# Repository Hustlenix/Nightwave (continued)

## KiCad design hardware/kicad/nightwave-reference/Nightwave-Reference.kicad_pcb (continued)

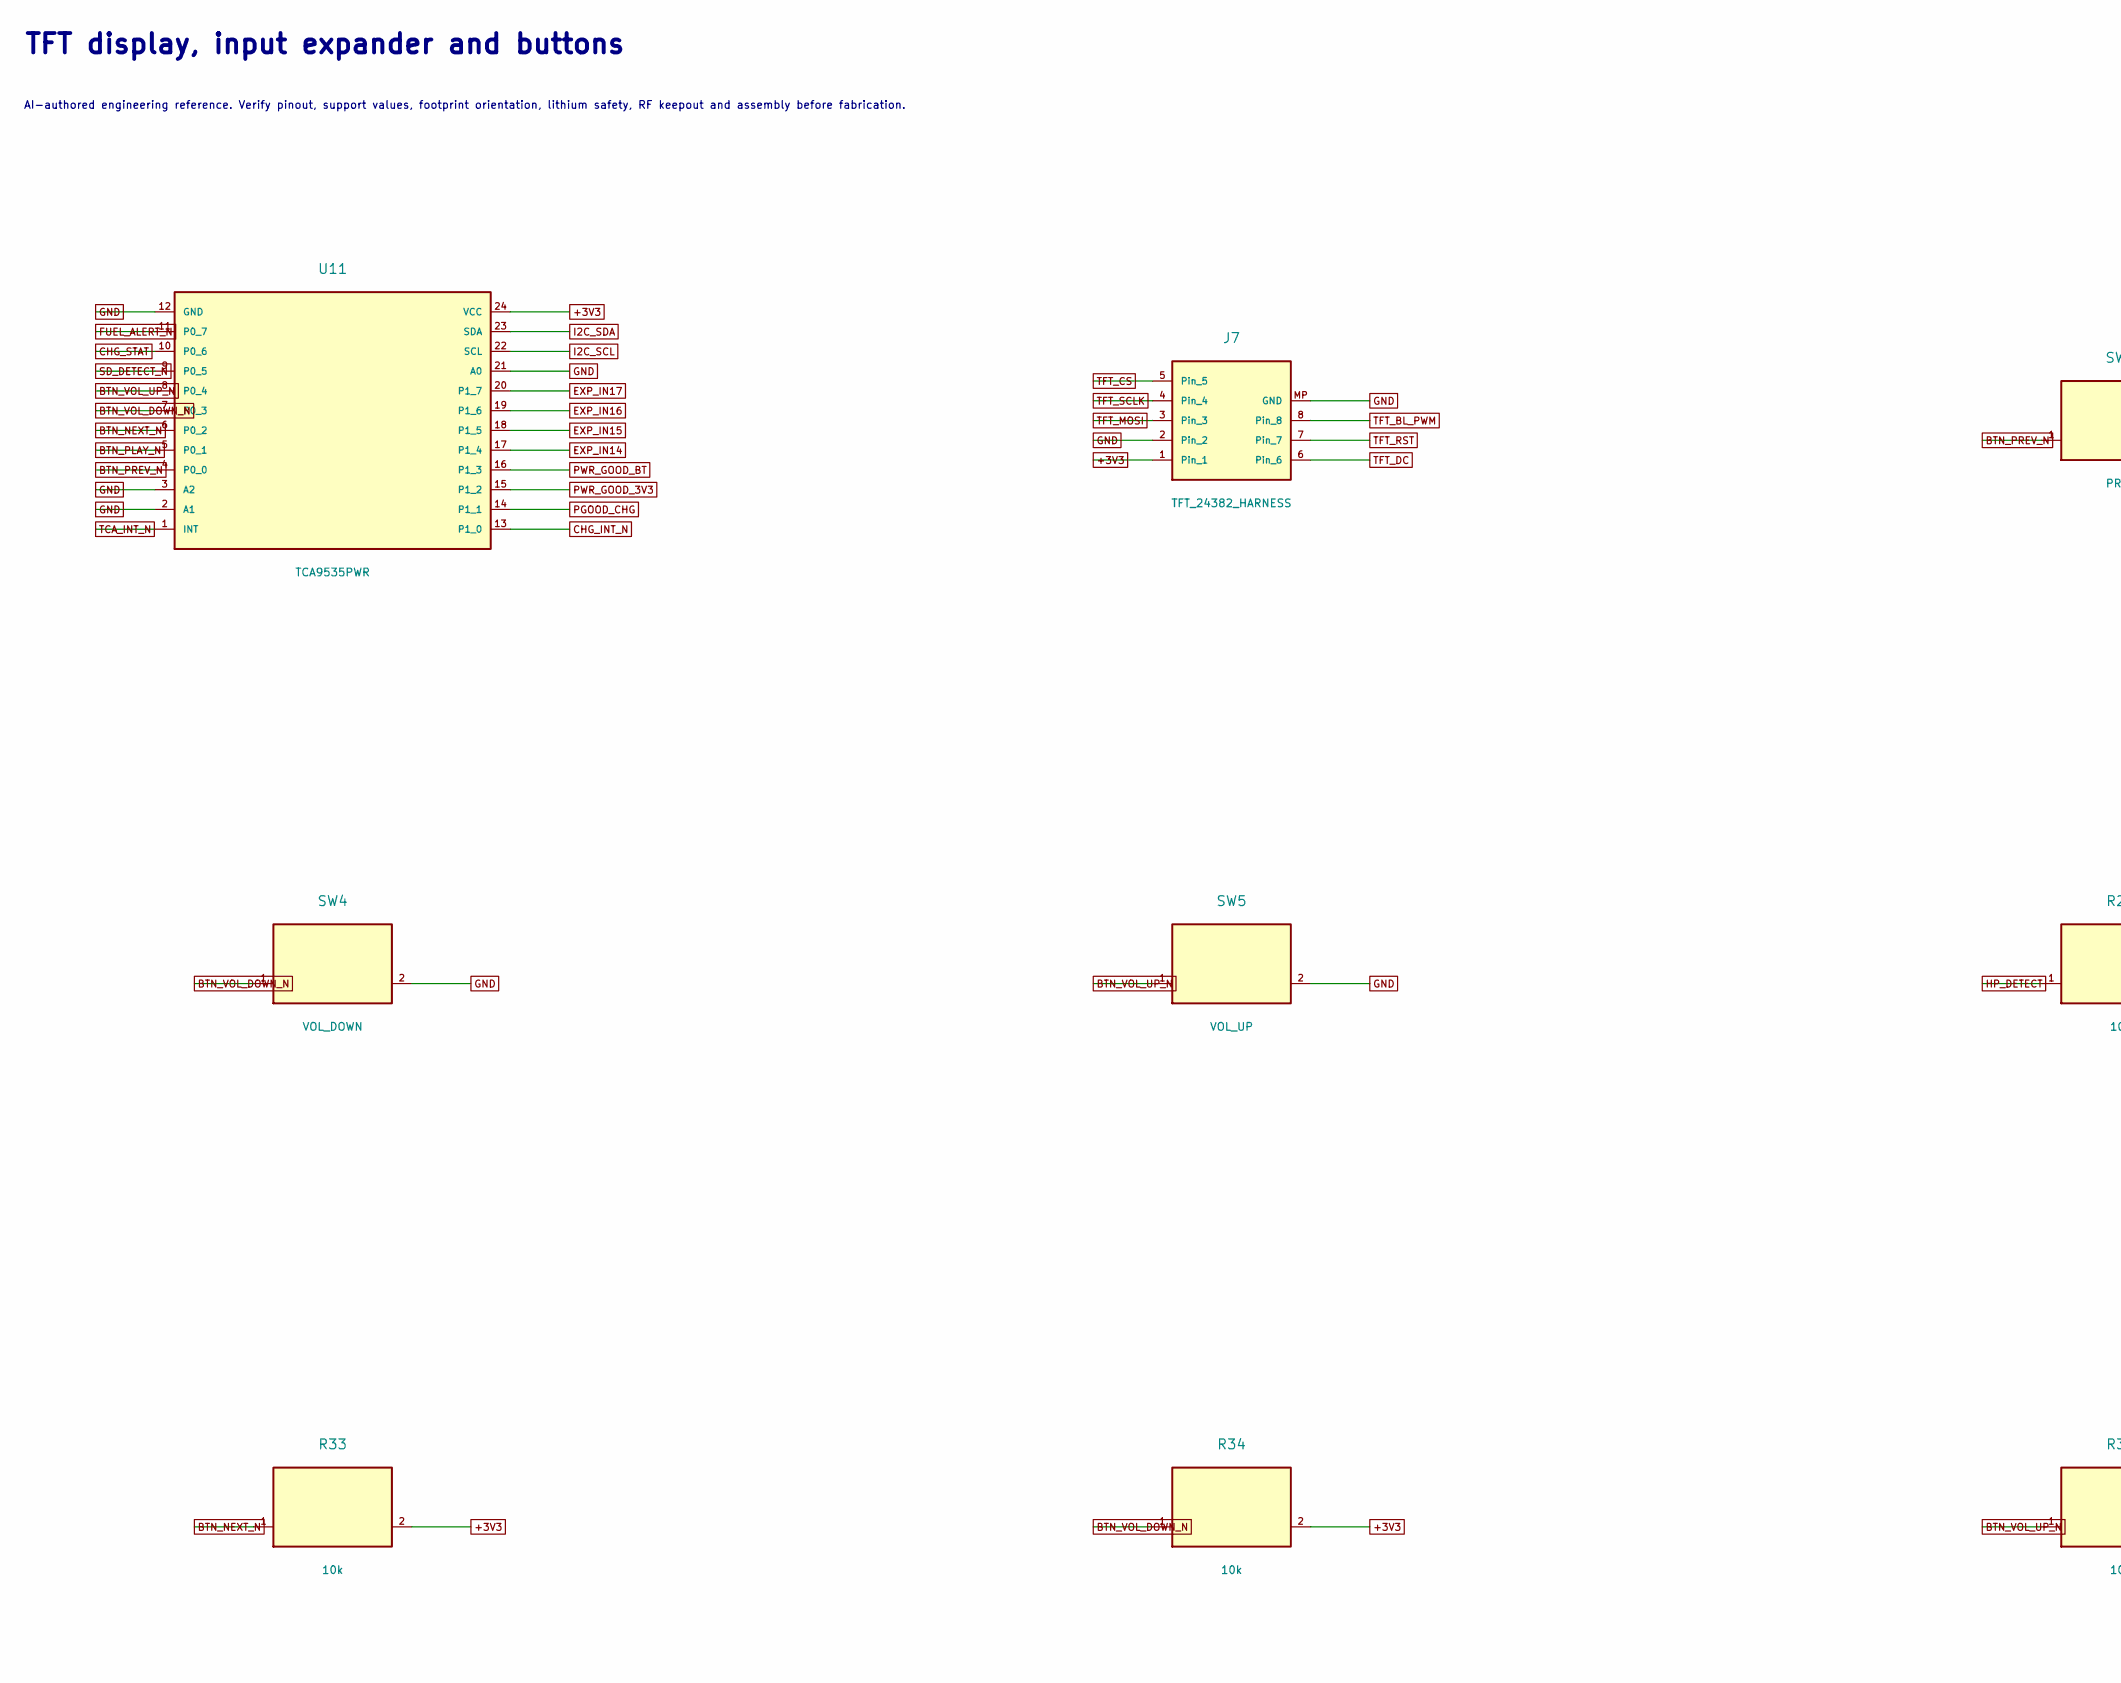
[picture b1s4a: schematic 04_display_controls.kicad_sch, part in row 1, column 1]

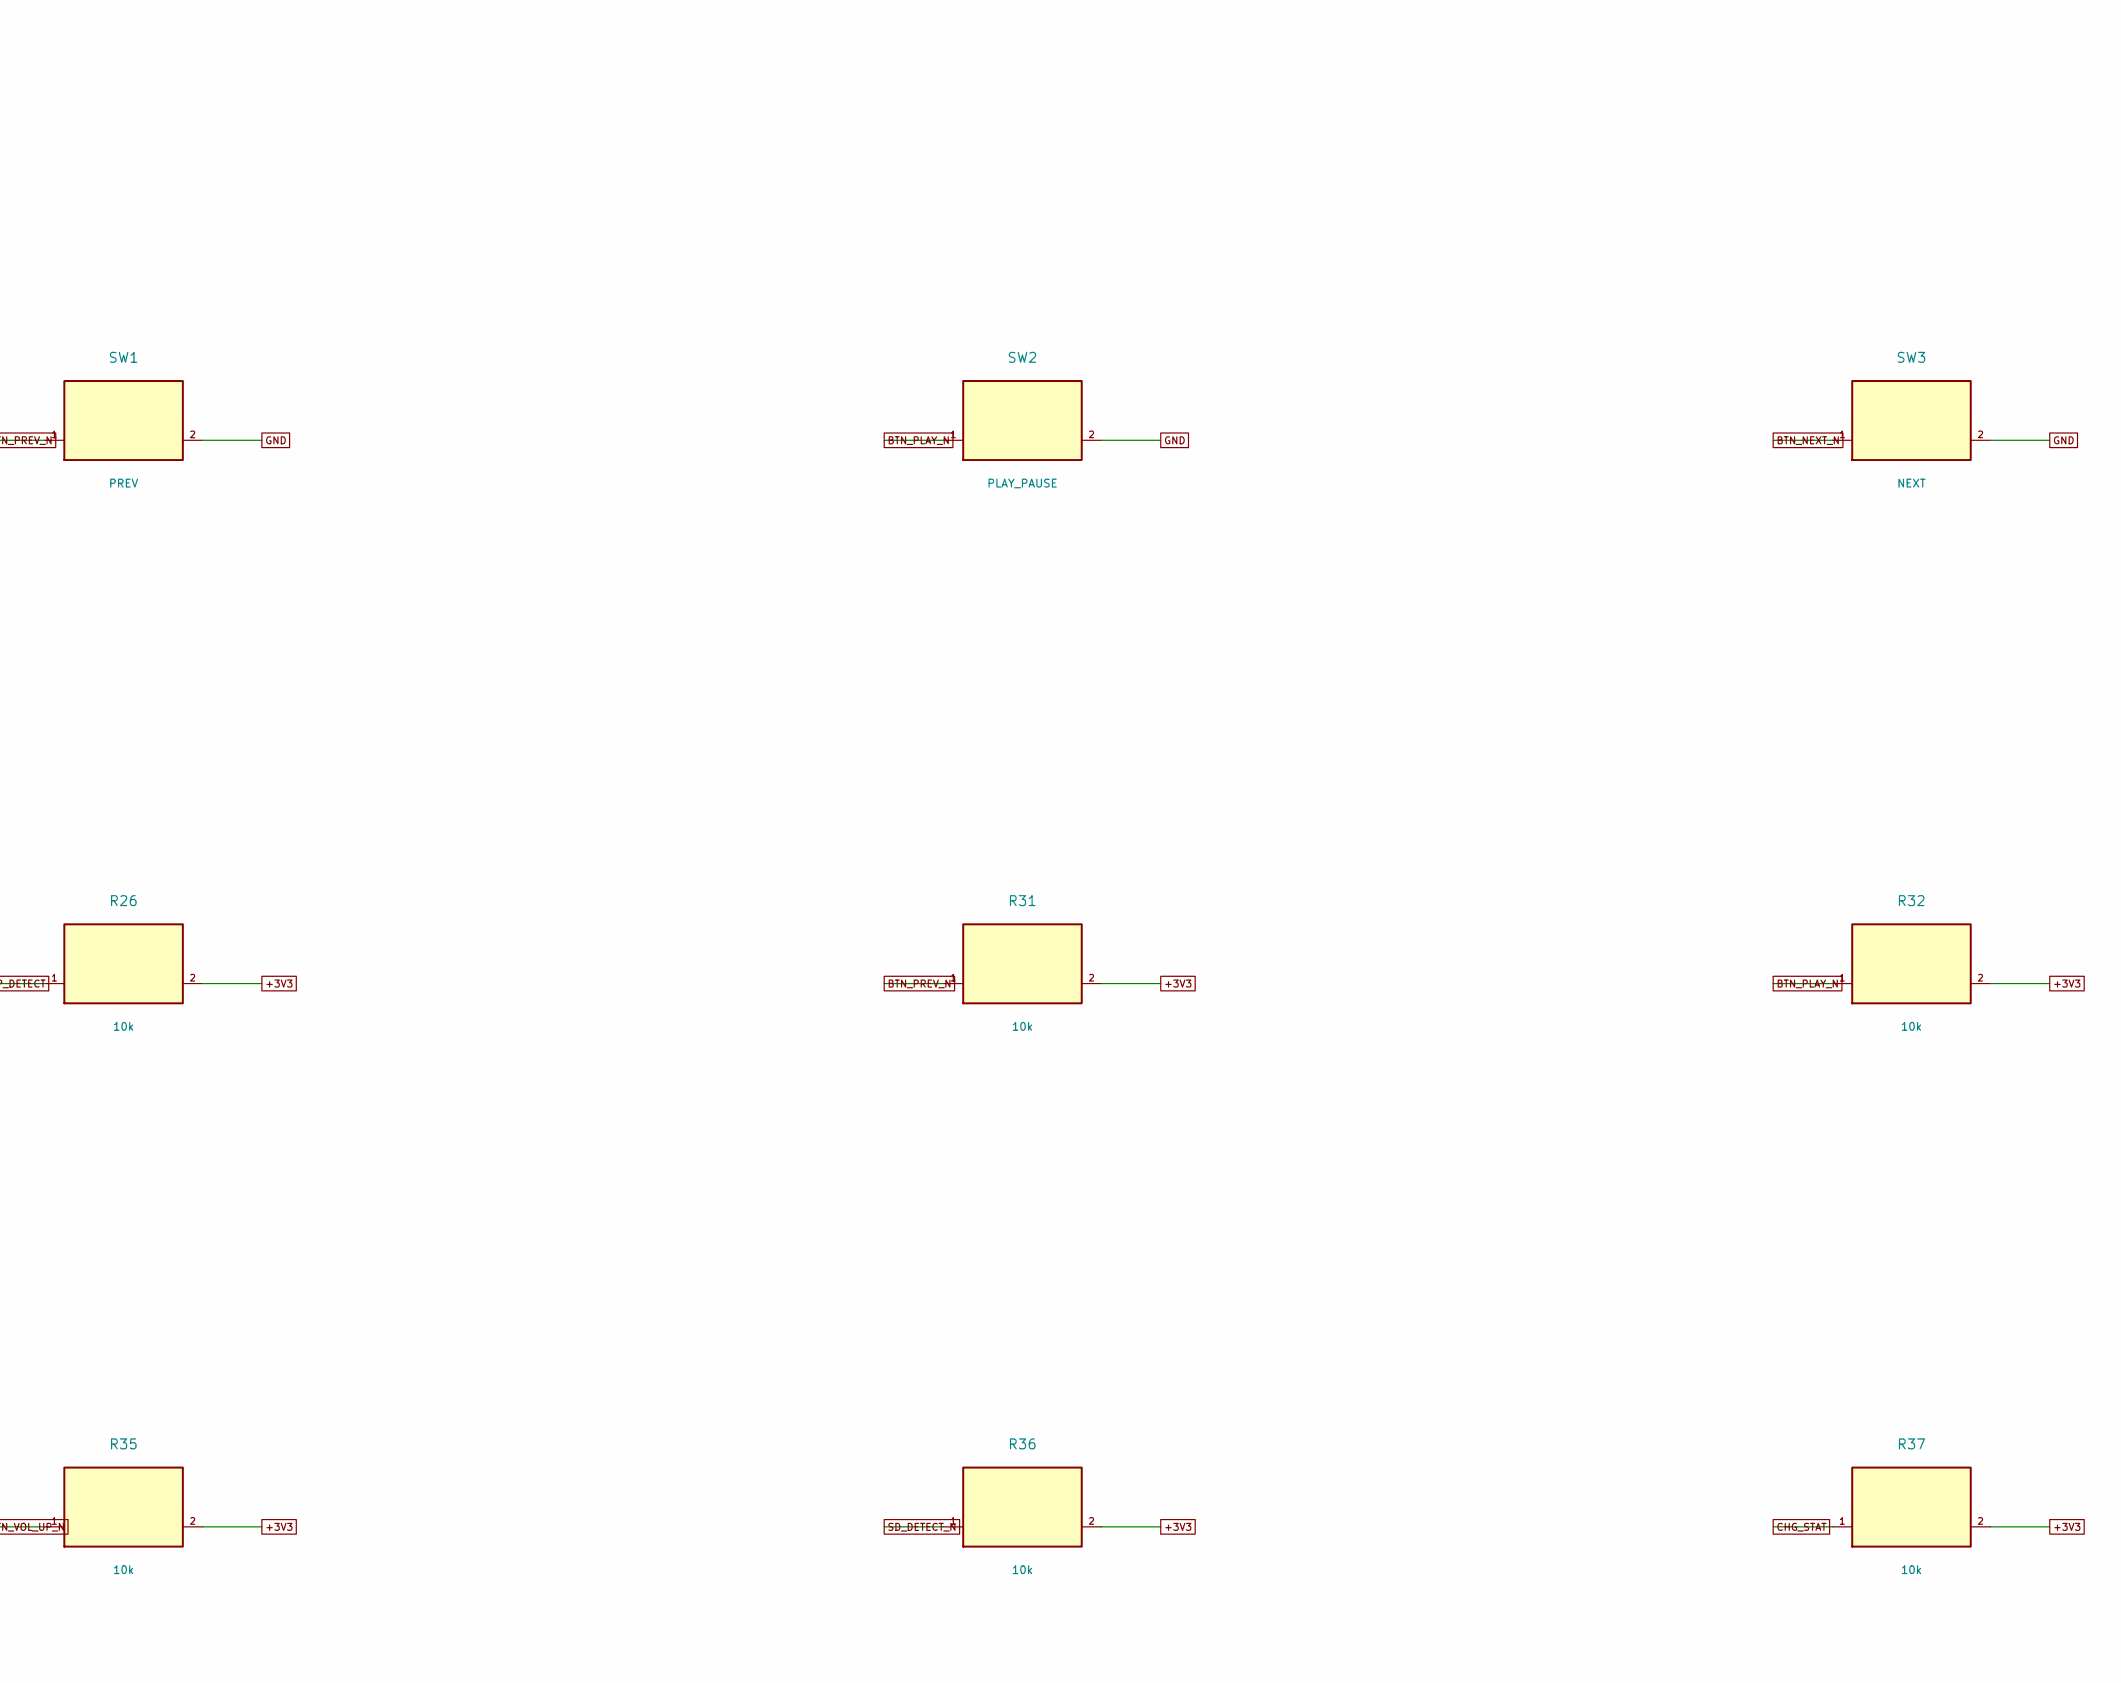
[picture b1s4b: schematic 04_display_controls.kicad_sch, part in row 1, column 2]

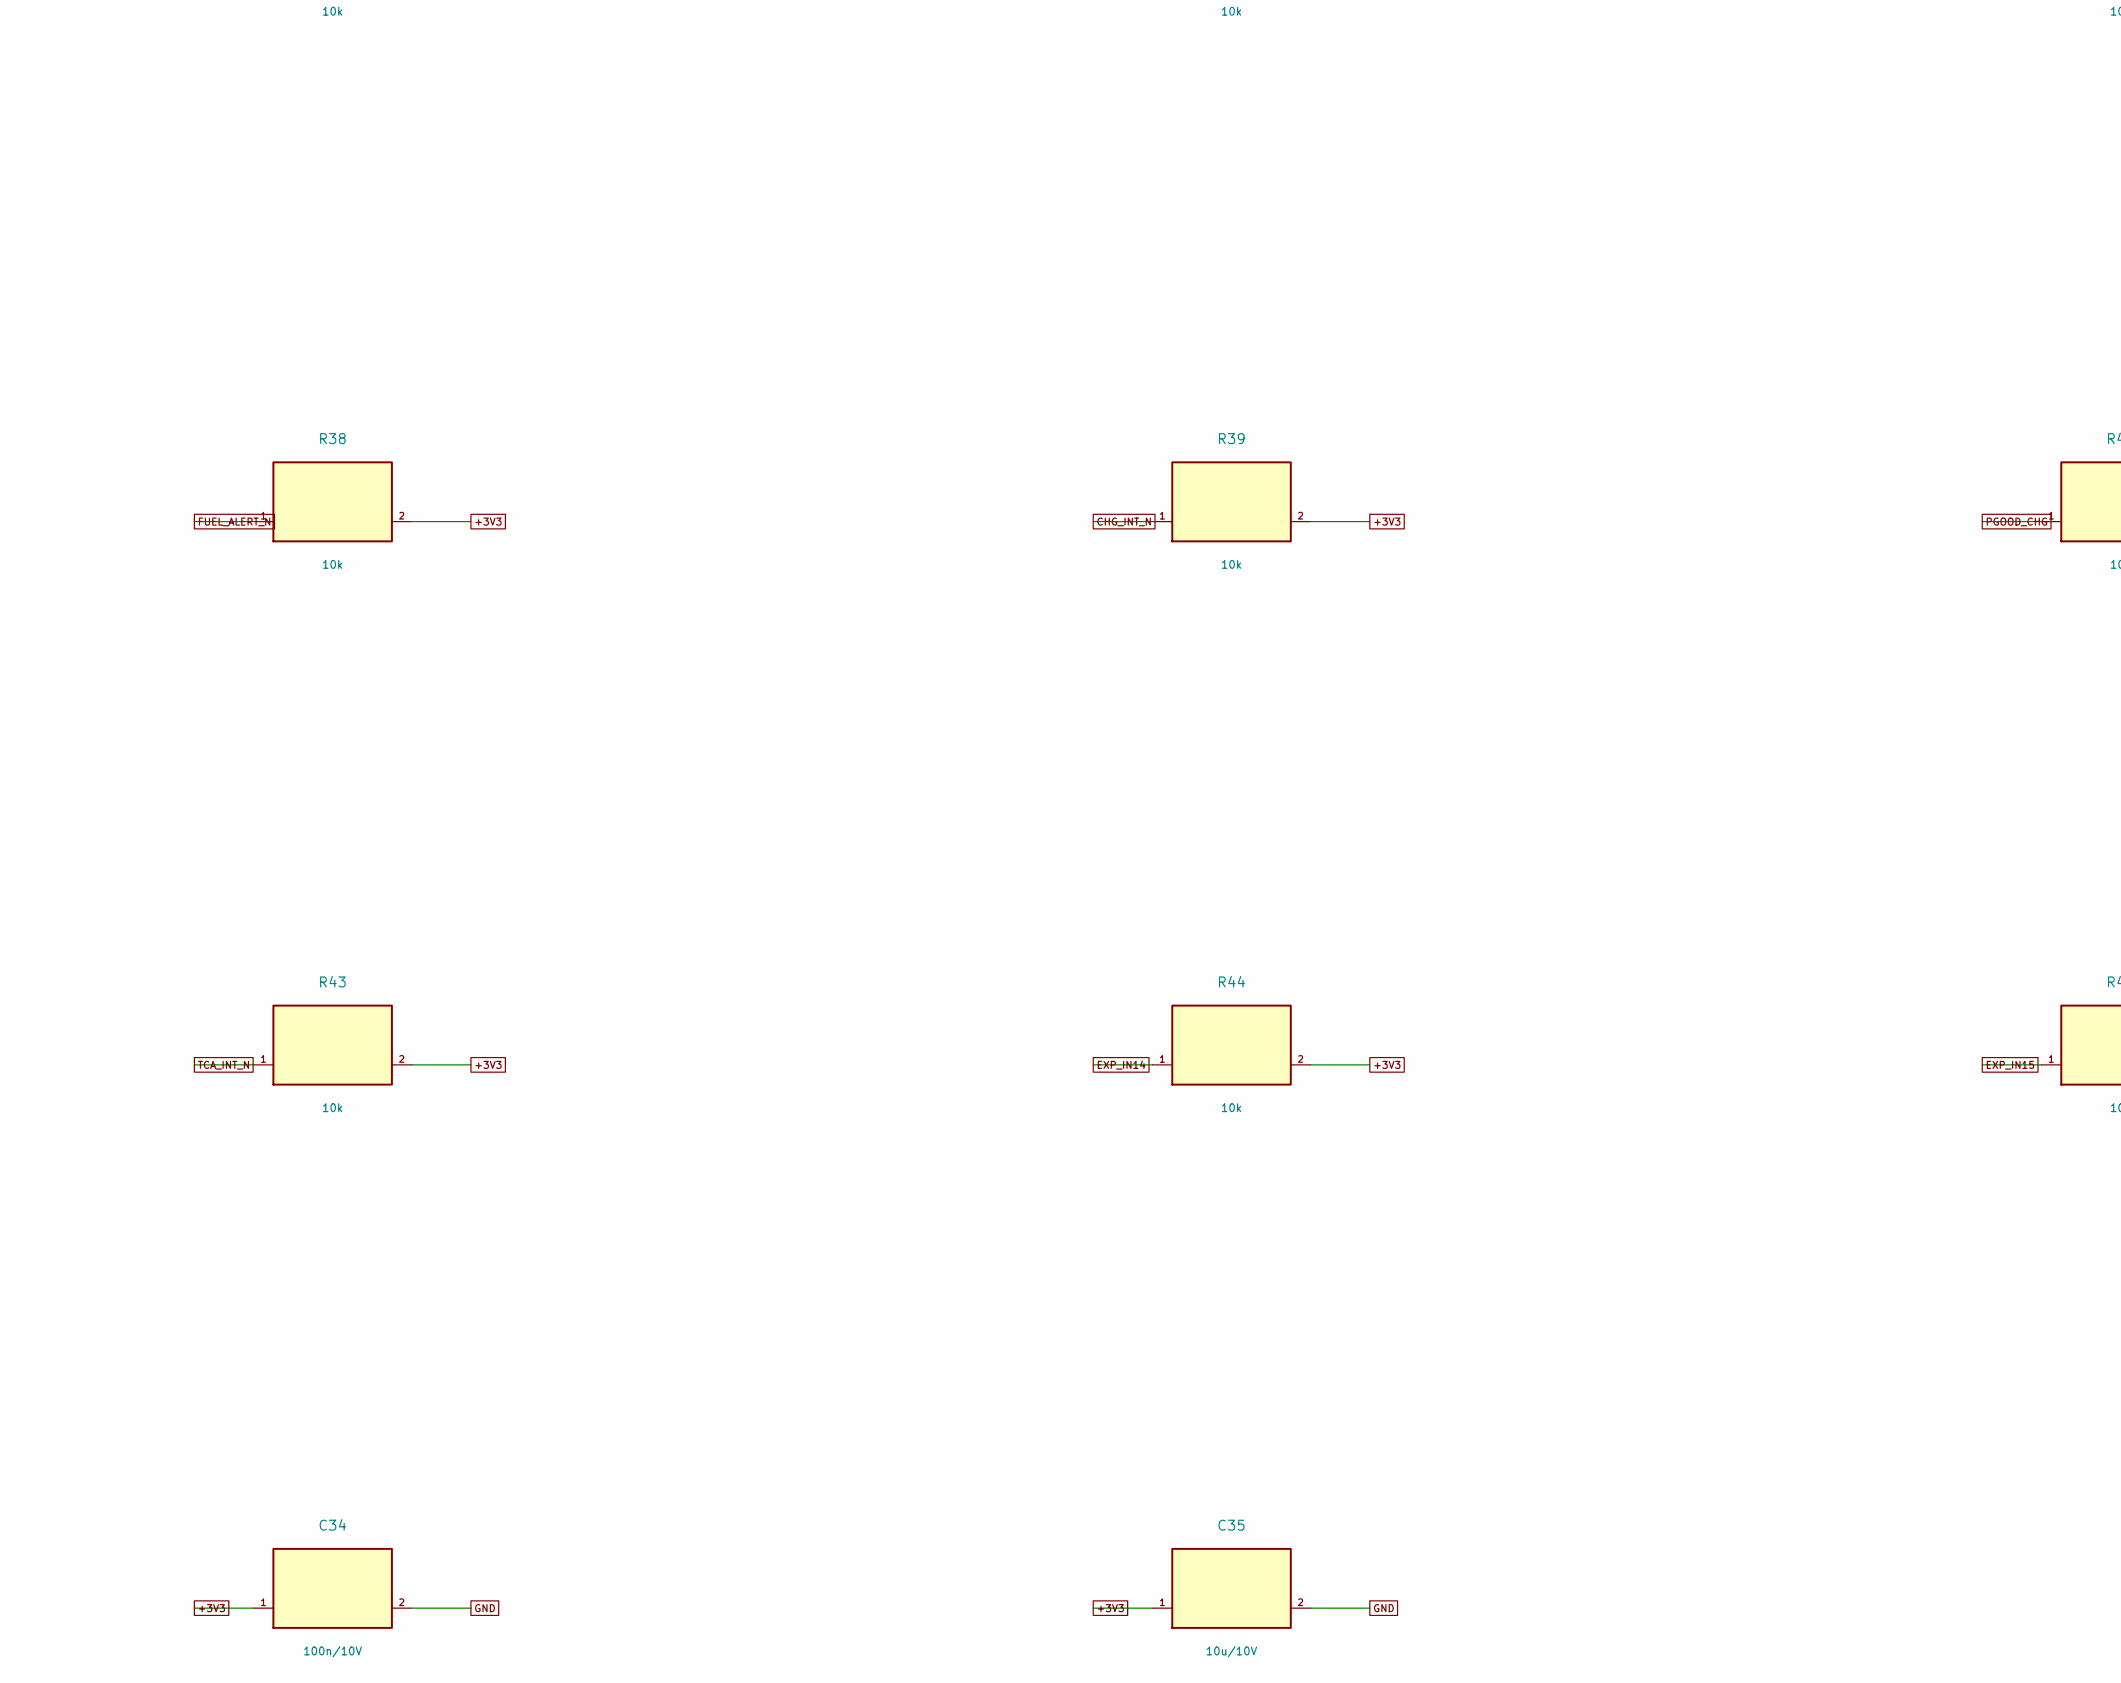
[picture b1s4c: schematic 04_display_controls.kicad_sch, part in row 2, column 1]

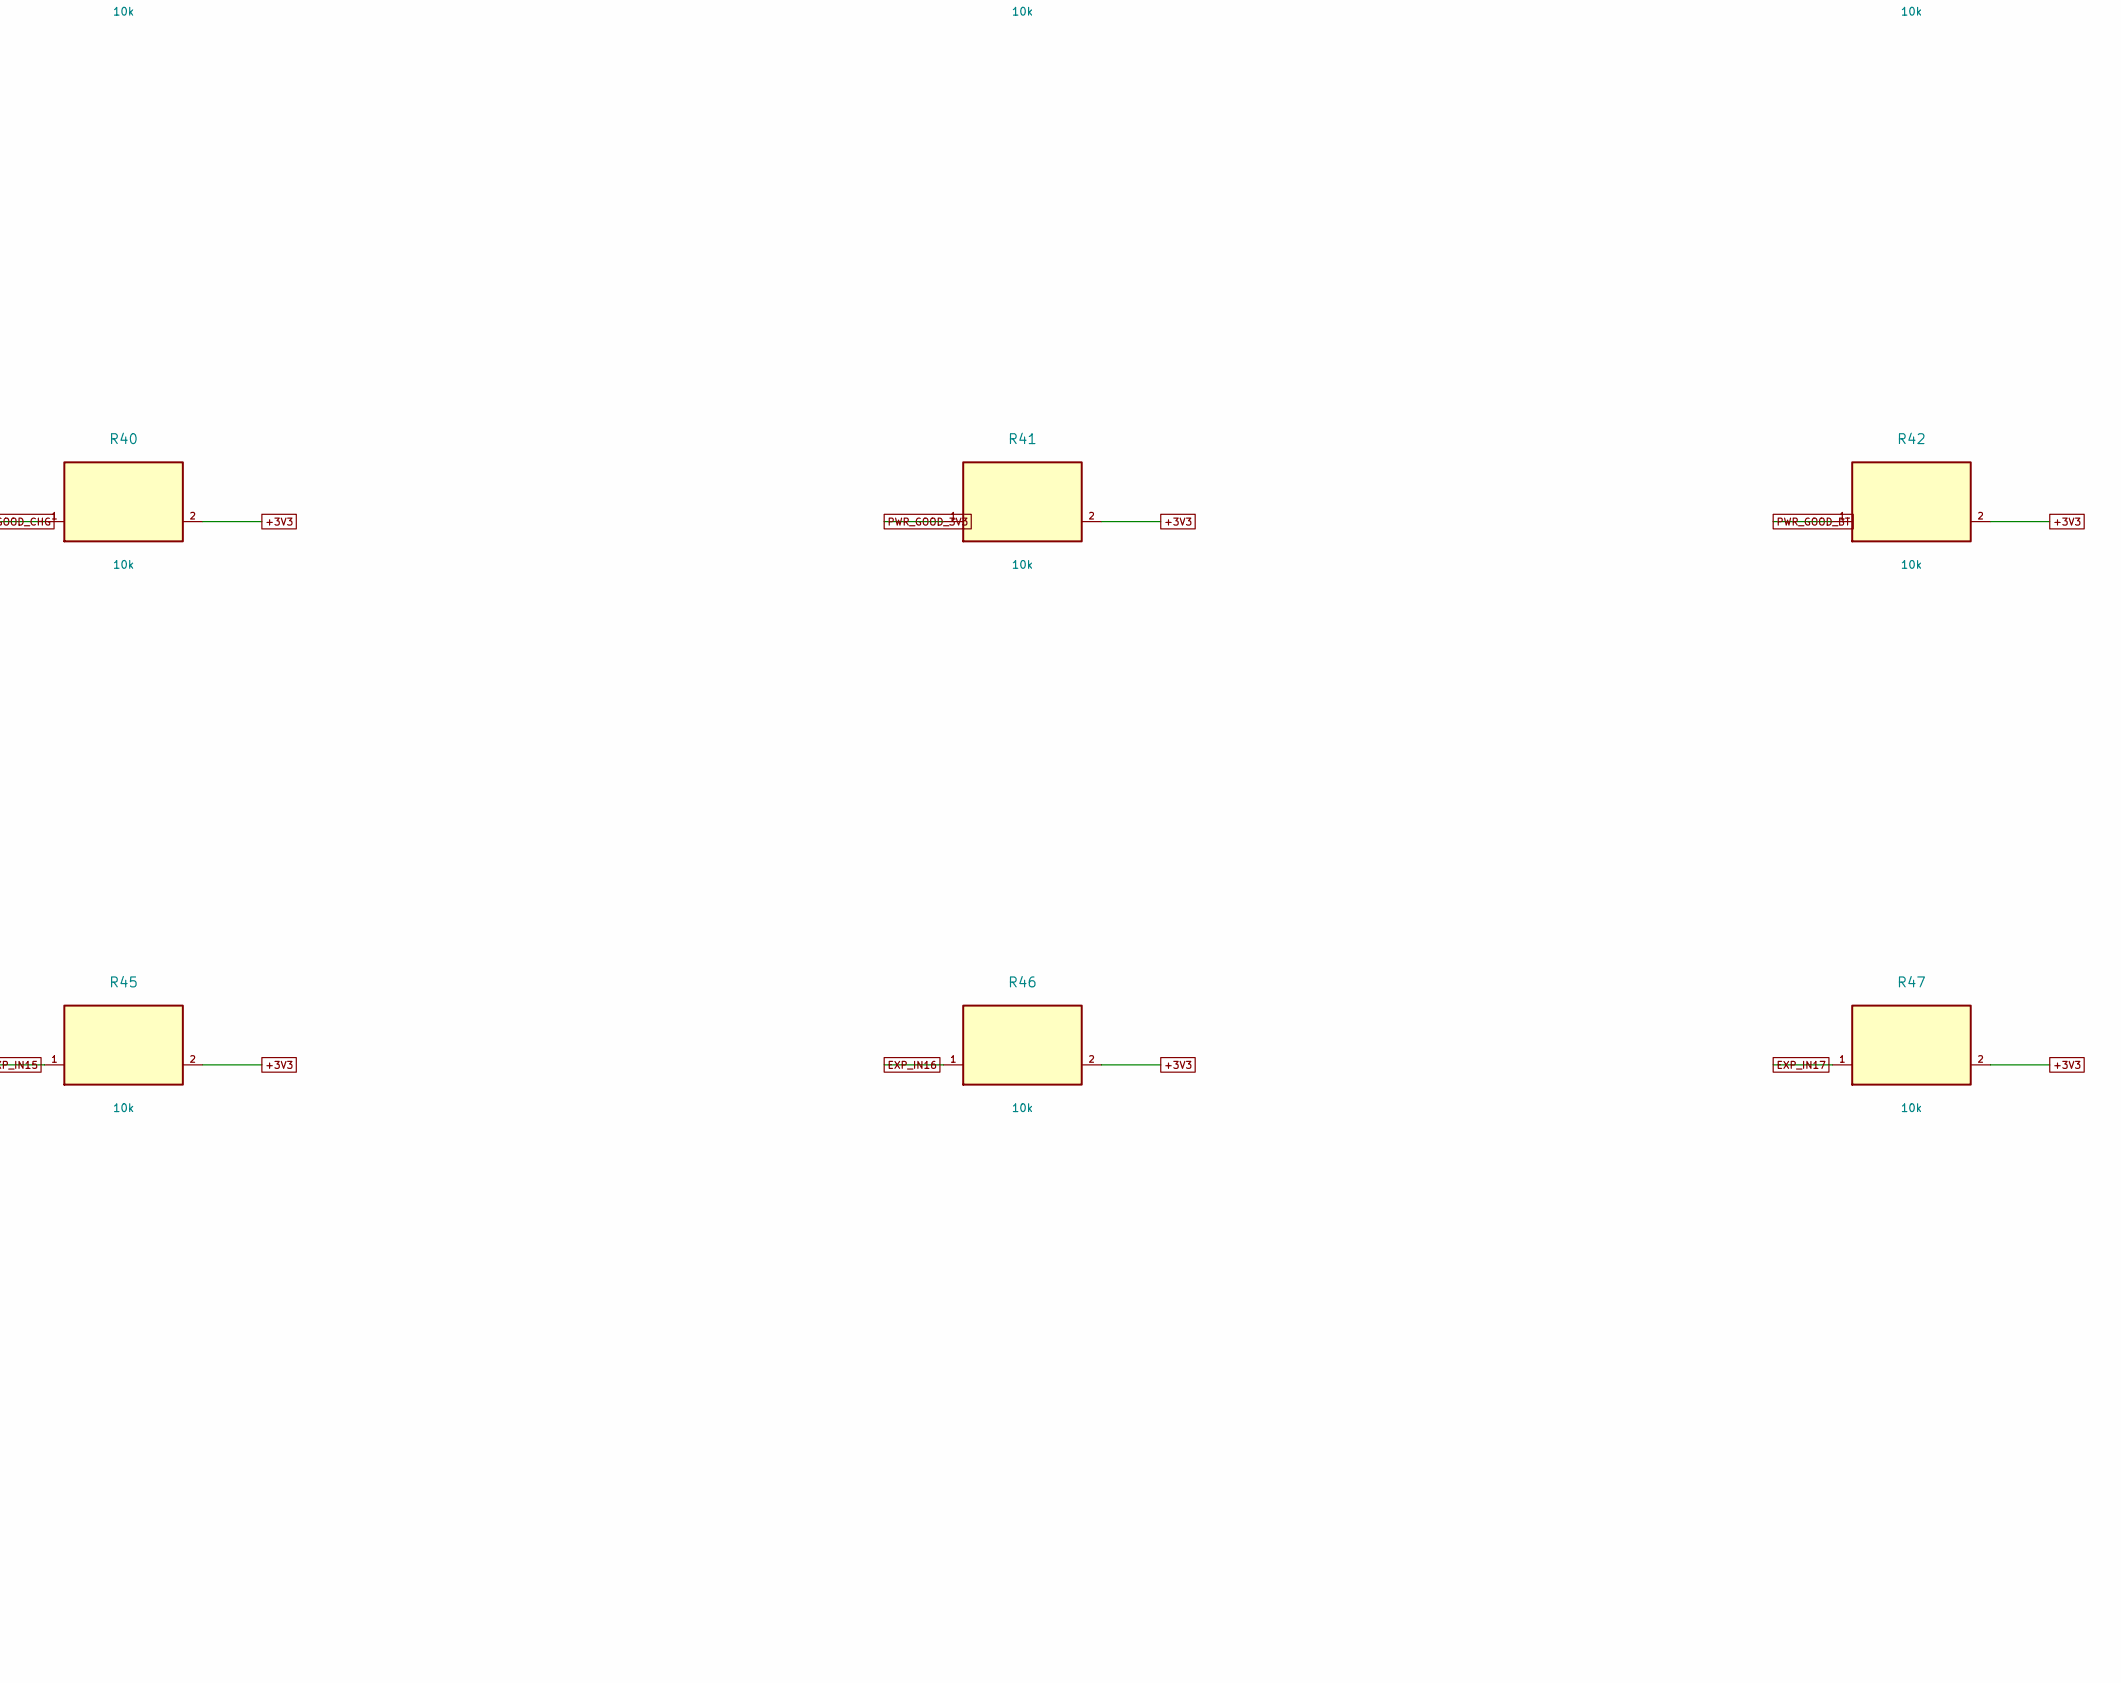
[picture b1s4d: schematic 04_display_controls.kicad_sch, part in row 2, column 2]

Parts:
C34: 100n/10V; C_0805_2012Metric
C35: 10u/10V; C_0805_2012Metric
J7: TFT_24382_HARNESS; JST_GH_SM08B-GHS-TB_1x08-1MP_P1.25mm_Horizontal
R26, R31, R32, R33, R34, R35, R36, R37, R38, R39, R40, R41, R42, R43, R44, R45, R46, R47: 10k; R_0603_1608Metric
SW1: PREV; SW_SPST_TL3342
SW2: PLAY_PAUSE; SW_SPST_TL3342
SW3: NEXT; SW_SPST_TL3342
SW4: VOL_DOWN; SW_SPST_TL3342
SW5: VOL_UP; SW_SPST_TL3342
U11: TCA9535PWR; TSSOP-24_4.4x7.8mm_P0.65mm

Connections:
+3V3: C34.1 (+3V3), C35.1 (+3V3), J7.1, R26.2 (+3V3), R31.2 (+3V3), R32.2 (+3V3), R33.2 (+3V3), R34.2 (+3V3), R35.2 (+3V3), R36.2 (+3V3), R37.2 (+3V3), R38.2 (+3V3), R39.2 (+3V3), R40.2 (+3V3), R41.2 (+3V3), R42.2 (+3V3), R43.2 (+3V3), R44.2 (+3V3), R45.2 (+3V3), R46.2 (+3V3), R47.2 (+3V3), U11.24 (VCC); also elsewhere on the board
BTN_NEXT_N: R33.1 (BTN_NEXT_N), SW3.1, U11.6 (P0_2)
BTN_PLAY_N: R32.1 (BTN_PLAY_N), SW2.1, U11.5 (P0_1)
BTN_PREV_N: R31.1 (BTN_PREV_N), SW1.1, U11.4 (P0_0)
BTN_VOL_DOWN_N: R34.1 (BTN_VOL_DOWN_N), SW4.1, U11.7 (P0_3)
BTN_VOL_UP_N: R35.1 (BTN_VOL_UP_N), SW5.1, U11.8 (P0_4)
CHG_INT_N: R39.1 (CHG_INT_N), U11.13 (P1_0); also elsewhere on the board
CHG_STAT: R37.1 (CHG_STAT), U11.10 (P0_6); also elsewhere on the board
EXP_IN14: R44.1 (EXP_IN14), U11.17 (P1_4)
EXP_IN15: R45.1 (EXP_IN15), U11.18 (P1_5)
EXP_IN16: R46.1 (EXP_IN16), U11.19 (P1_6)
EXP_IN17: R47.1 (EXP_IN17), U11.20 (P1_7)
FUEL_ALERT_N: R38.1 (FUEL_ALERT_N), U11.11 (P0_7); also elsewhere on the board
GND: C34.2 (GND), C35.2 (GND), J7.2, J7.MP (GND), SW1.2, SW2.2, SW3.2, SW4.2, SW5.2, U11.2 (A1), U11.3 (A2), U11.12 (GND), U11.21 (A0); also elsewhere on the board
HP_DETECT: R26.1 (HP_DETECT); also elsewhere on the board
I2C_SCL: U11.22 (SCL); also elsewhere on the board
I2C_SDA: U11.23 (SDA); also elsewhere on the board
PGOOD_CHG: R40.1 (PGOOD_CHG), U11.14 (P1_1); also elsewhere on the board
PWR_GOOD_3V3: R41.1 (PWR_GOOD_3V3), U11.15 (P1_2); also elsewhere on the board
PWR_GOOD_BT: R42.1 (PWR_GOOD_BT), U11.16 (P1_3); also elsewhere on the board
SD_DETECT_N: R36.1 (SD_DETECT_N), U11.9 (P0_5); also elsewhere on the board
TCA_INT_N: R43.1 (TCA_INT_N), U11.1 (INT); also elsewhere on the board
TFT_BL_PWM: J7.8; also elsewhere on the board
TFT_CS: J7.5; also elsewhere on the board
TFT_DC: J7.6; also elsewhere on the board
TFT_MOSI: J7.3; also elsewhere on the board
TFT_RST: J7.7; also elsewhere on the board
TFT_SCLK: J7.4; also elsewhere on the board

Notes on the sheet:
TFT display, input expander and buttons
AI-authored engineering reference. Verify pinout, support values, footprint orientation, lithium safety, RF keepout and assembly before fabrication.

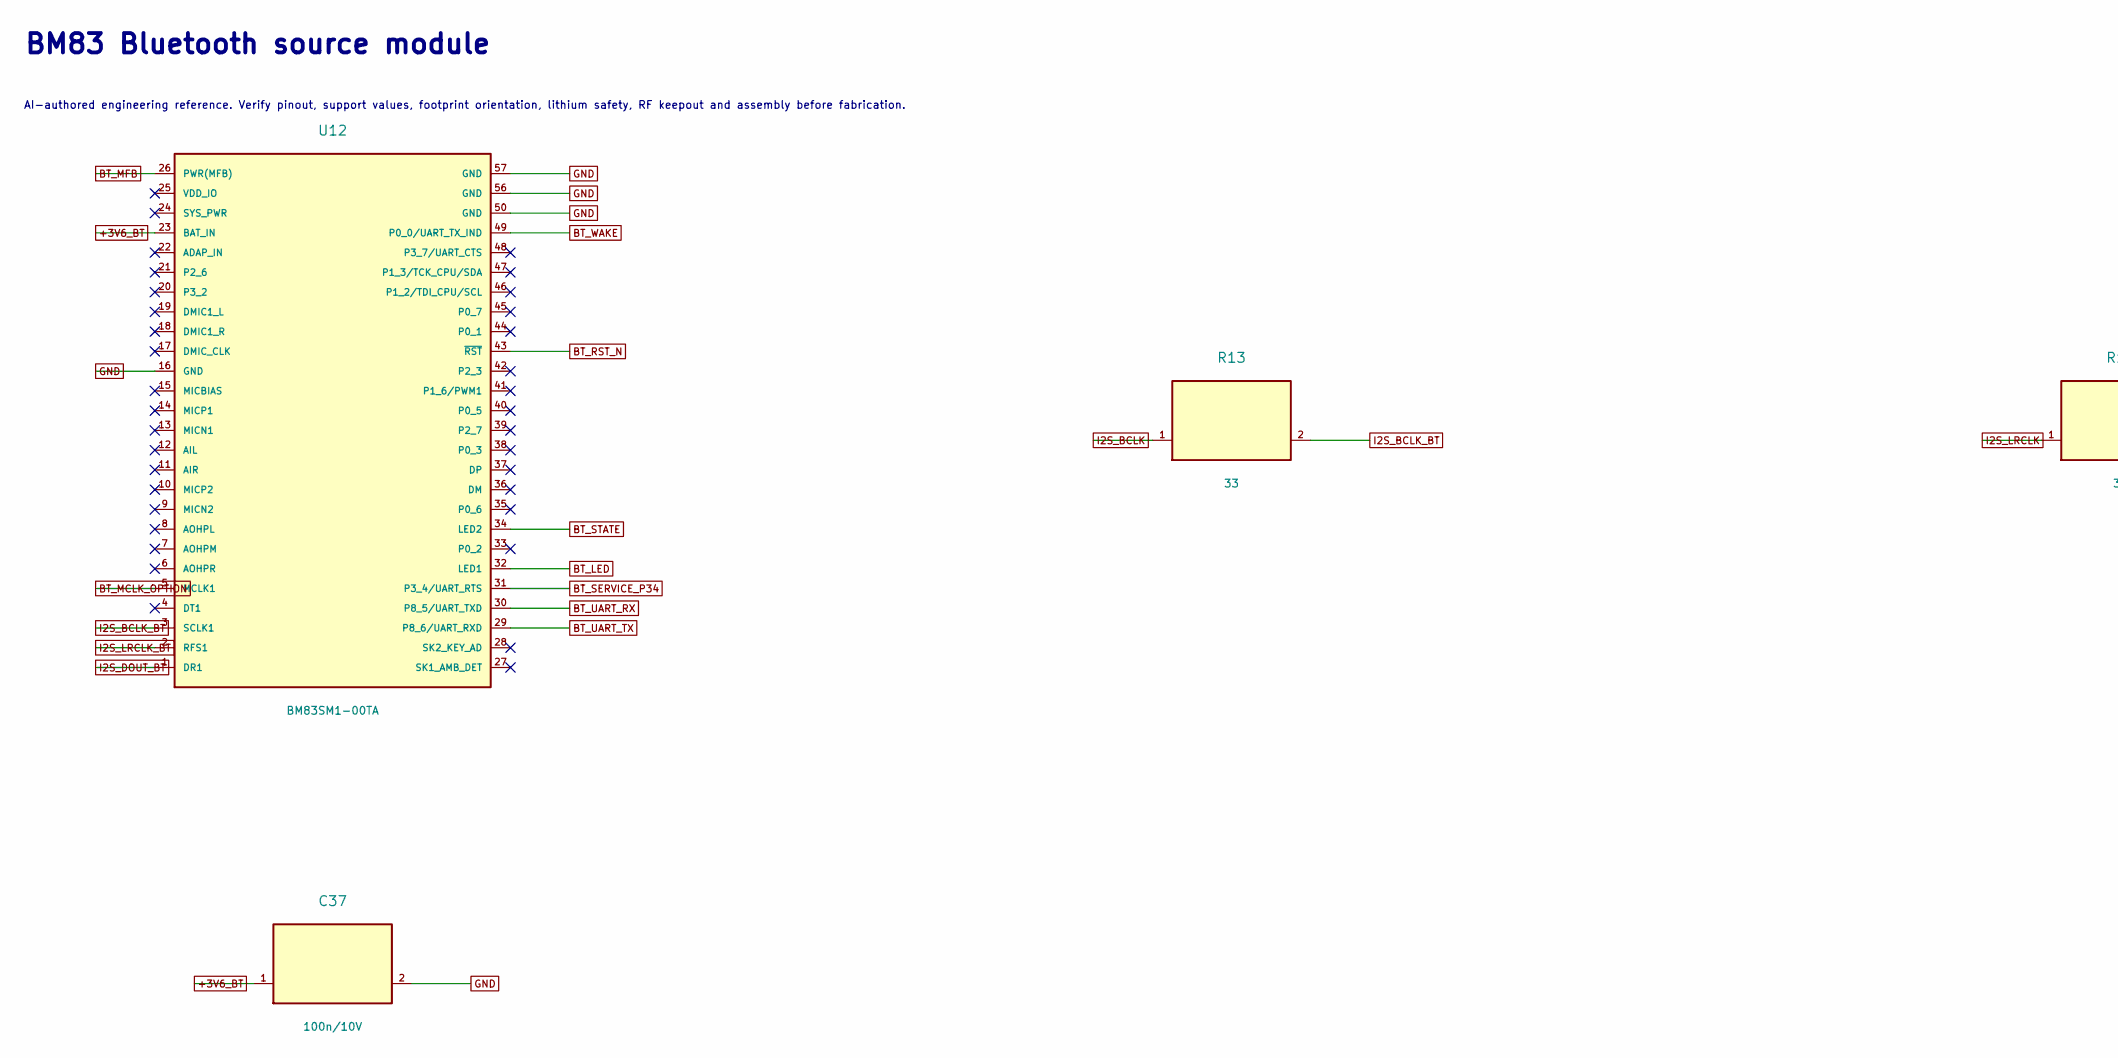
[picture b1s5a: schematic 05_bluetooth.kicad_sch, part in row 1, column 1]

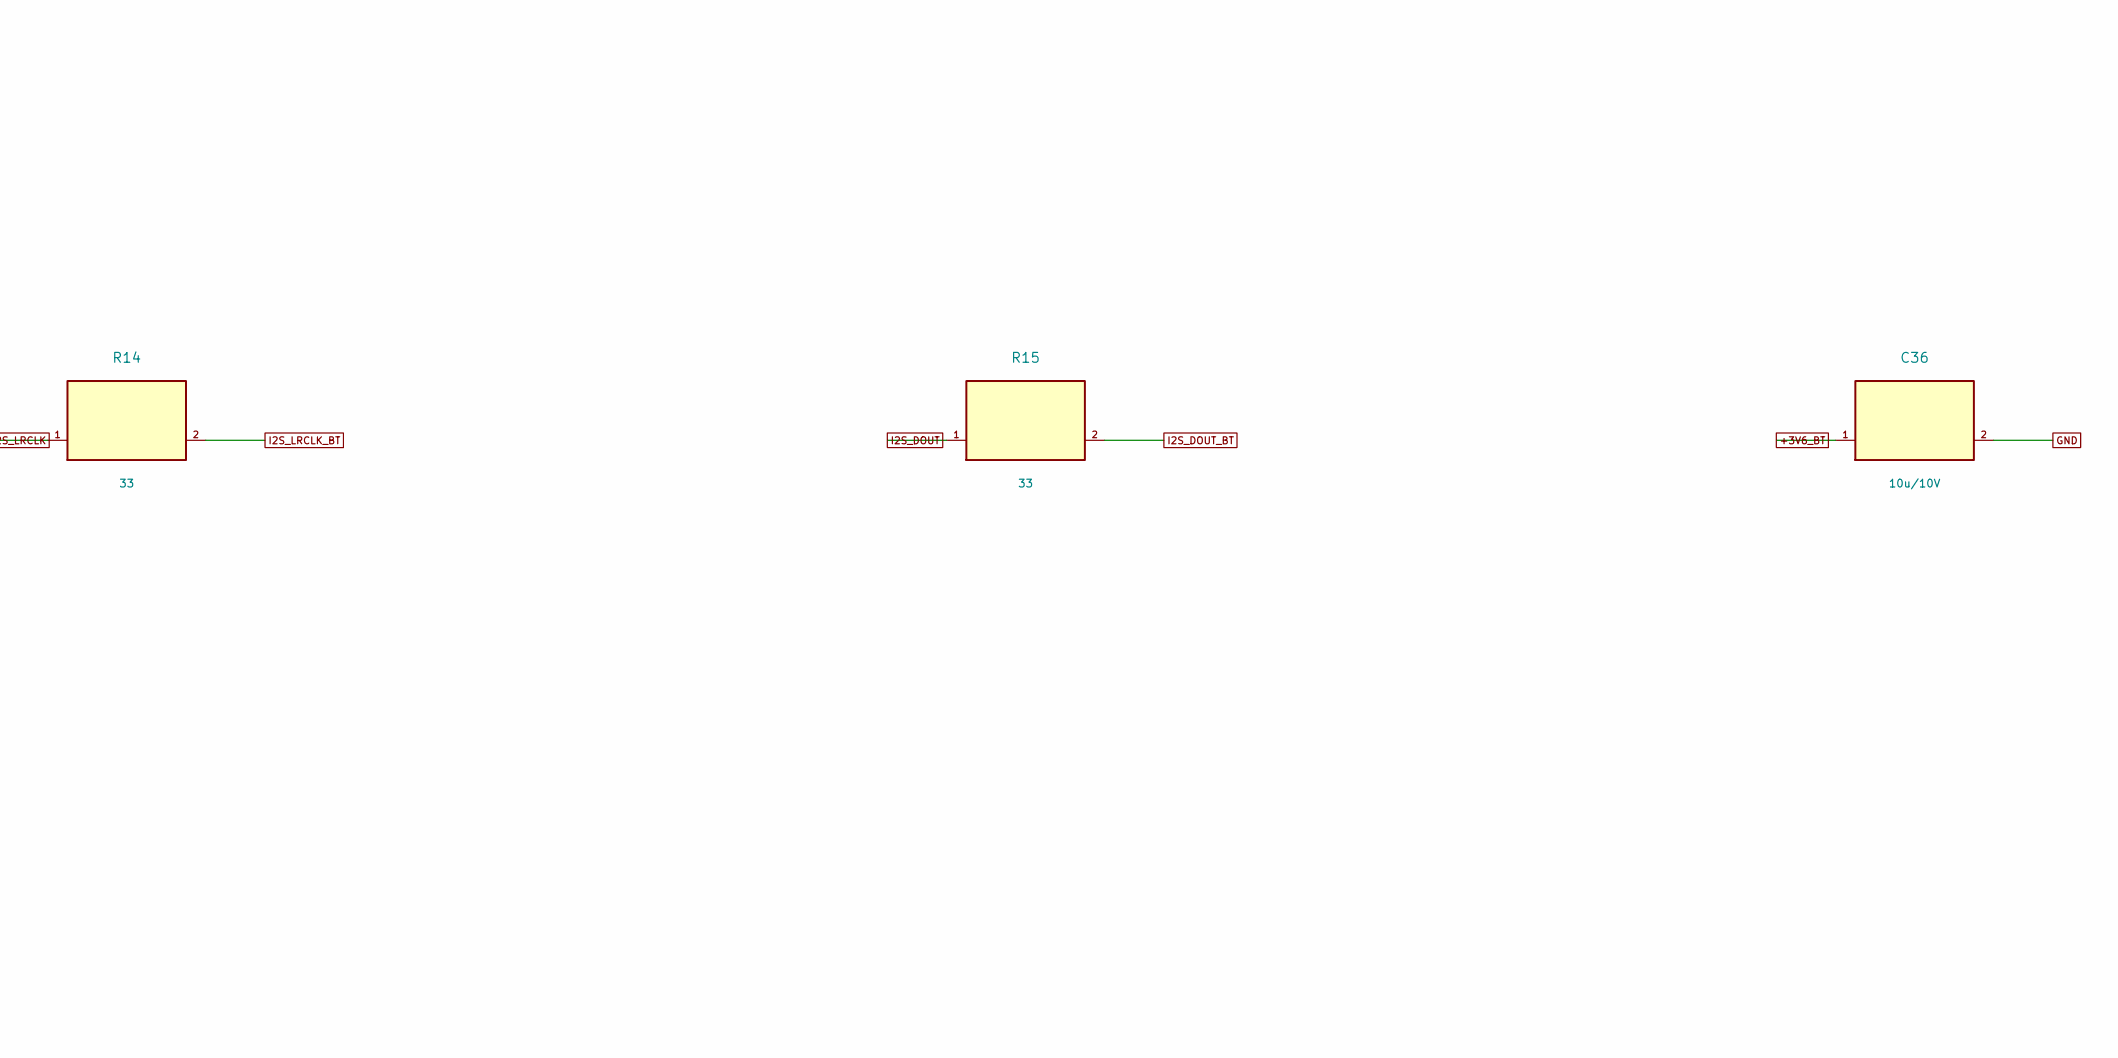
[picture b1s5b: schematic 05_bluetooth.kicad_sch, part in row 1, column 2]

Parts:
C36: 10u/10V; C_0805_2012Metric
C37: 100n/10V; C_0805_2012Metric
R13, R14, R15: 33; R_0603_1608Metric
U12: BM83SM1-00TA; Microchip_BM83_GroundLands

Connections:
+3V6_BT: C36.1 (+3V6_BT), C37.1 (+3V6_BT), U12.23 (BAT_IN); also elsewhere on the board
BT_LED: U12.32 (LED1); also elsewhere on the board
BT_MCLK_OPTION: U12.5 (MCLK1); also elsewhere on the board
BT_MFB: U12.26 (PWR(MFB)); also elsewhere on the board
BT_RST_N: U12.43 (~RST); also elsewhere on the board
BT_SERVICE_P34: U12.31 (P3_4/UART_RTS); also elsewhere on the board
BT_STATE: U12.34 (LED2); also elsewhere on the board
BT_UART_RX: U12.30 (P8_5/UART_TXD); also elsewhere on the board
BT_UART_TX: U12.29 (P8_6/UART_RXD); also elsewhere on the board
BT_WAKE: U12.49 (P0_0/UART_TX_IND); also elsewhere on the board
GND: C36.2 (GND), C37.2 (GND), U12.16 (GND), U12.50 (GND), U12.56 (GND), U12.57 (GND); also elsewhere on the board
I2S_BCLK: R13.1 (I2S_BCLK); also elsewhere on the board
I2S_BCLK_BT: R13.2 (I2S_BCLK_BT), U12.3 (SCLK1)
I2S_DOUT: R15.1 (I2S_DOUT); also elsewhere on the board
I2S_DOUT_BT: R15.2 (I2S_DOUT_BT), U12.1 (DR1)
I2S_LRCLK: R14.1 (I2S_LRCLK); also elsewhere on the board
I2S_LRCLK_BT: R14.2 (I2S_LRCLK_BT), U12.2 (RFS1)

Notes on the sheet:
BM83 Bluetooth source module
AI-authored engineering reference. Verify pinout, support values, footprint orientation, lithium safety, RF keepout and assembly before fabrication.
